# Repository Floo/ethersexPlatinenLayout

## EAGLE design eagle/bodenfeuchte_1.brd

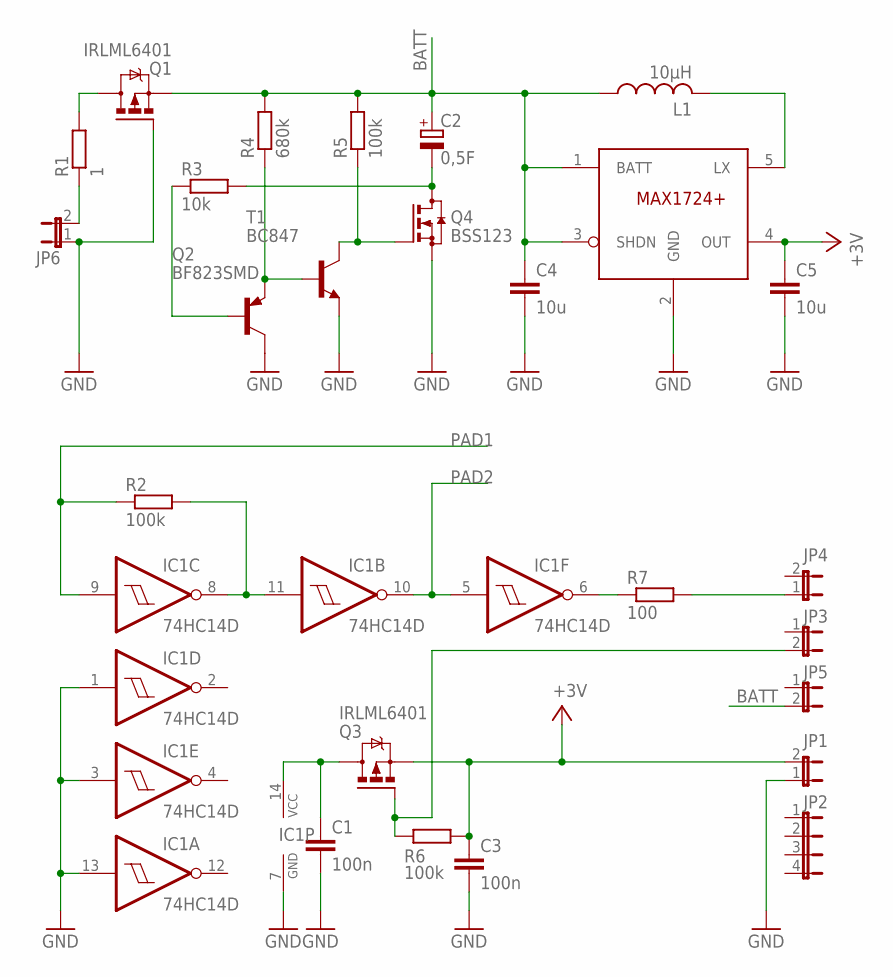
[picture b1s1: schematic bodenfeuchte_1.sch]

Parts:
C1, C3: 100n; C0805
C2: 0,5F; GOLDCAP5-21.5
C4, C5: 10u; C0805
IC1: 74HC14D; SO14
JP1, JP3, JP4, JP5, JP6: JP1E; JP1
JP2: JP4E; JP4
L1: 10µH; L1812
Q1, Q3: IRLML6401; MICRO3
Q2: BF823SMD; SOT23-BEC
Q4: BSS123; SOT23
R1: 1; R0805
R2, R5, R6: 100k; R0805
R3: 10k; R0805
R4: 680k; R0805
R7: 100; R0805
T1: BC847; SOT23
U$1: MAX1724; SOT23-5L

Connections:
BATT: C2.+, C4.1, JP5.2, L1.1, Q1.2 (S), R4.2, R5.2, U$1.1 (BATT), U$1.3 (SHDN)
GND: C1.2, C3.2, C4.2, C5.2, IC1.1 (I), IC1.3 (I), IC1.7 (GND), IC1.13 (I), JP1.1, JP6.1, Q1.1 (G), Q2.C, Q4.2 (S), T1.2 (E), U$1.2 (GND)
unnamed: IC1.8 (O), IC1.11 (I), R2.2
unnamed: IC1.6 (O), R7.1
unnamed: JP4.1, R7.2
unnamed: JP3.2, Q3.1 (G), R6.1
unnamed: C1.1, IC1.14 (VCC), Q3.3 (D)
unnamed: Q4.1 (G), R5.1, T1.3 (C)
unnamed: Q2.E, R4.1, T1.1 (B)
unnamed: C2.-, Q4.3 (D), R3.2
unnamed: Q2.B, R3.1
unnamed: JP6.2, R1.1
unnamed: Q1.3 (D), R1.2
unnamed: L1.2, U$1.5 (LX)
PAD1: IC1.9 (I), R2.1
PAD2: IC1.5 (I), IC1.10 (O)
V+: C3.1, C5.1, JP1.2, Q3.2 (S), R6.2, U$1.4 (OUT)

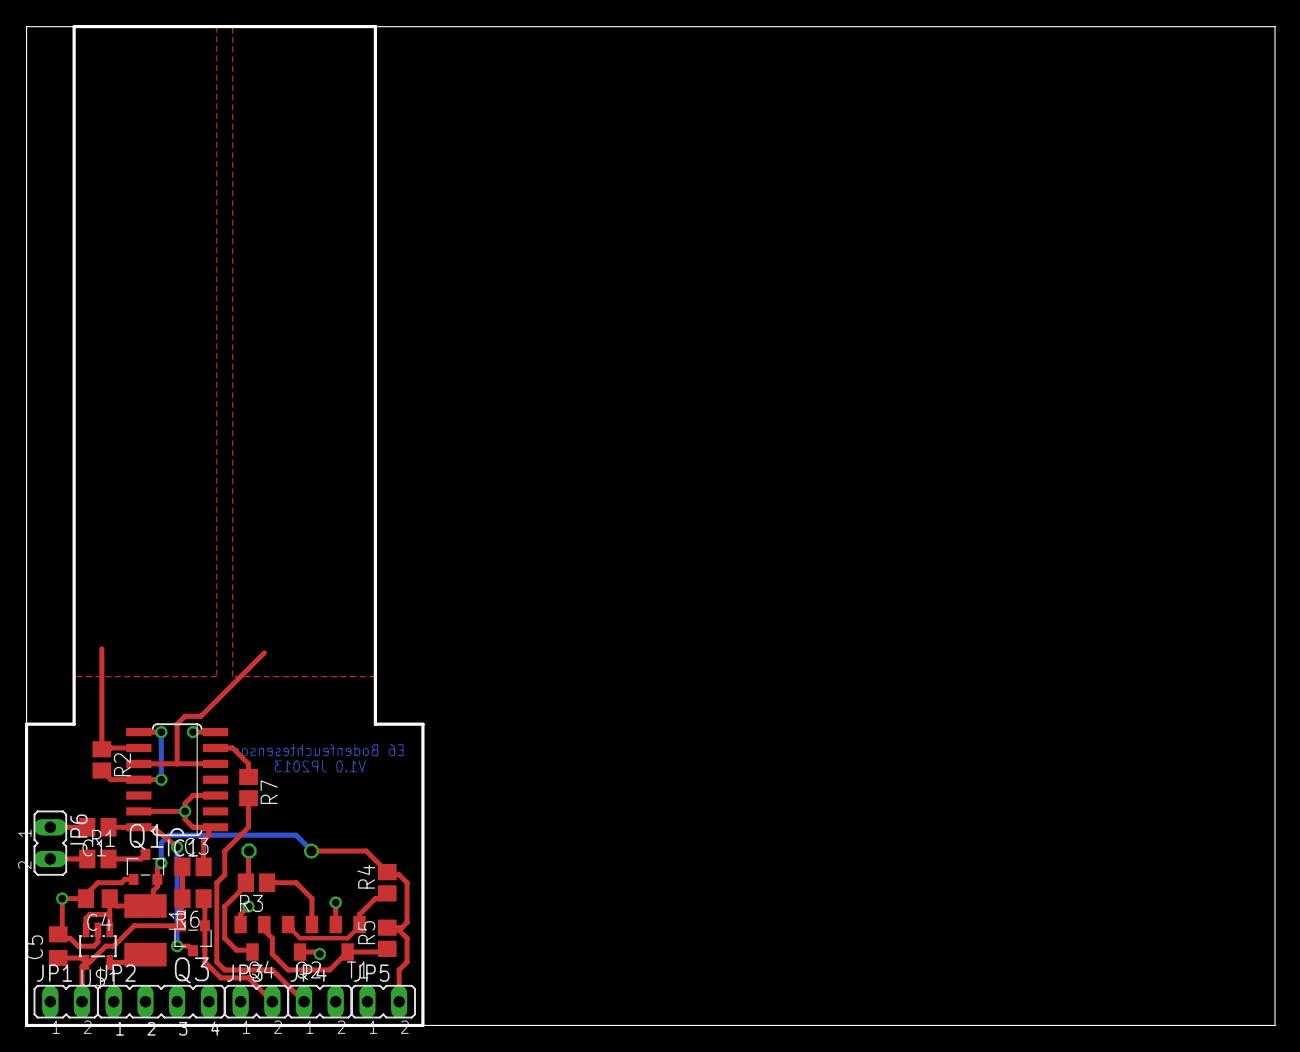
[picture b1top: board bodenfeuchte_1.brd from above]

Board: 2 copper layers, 99.9 x 80.0 mm, 26 parts (1 on the bottom side), 17 nets.

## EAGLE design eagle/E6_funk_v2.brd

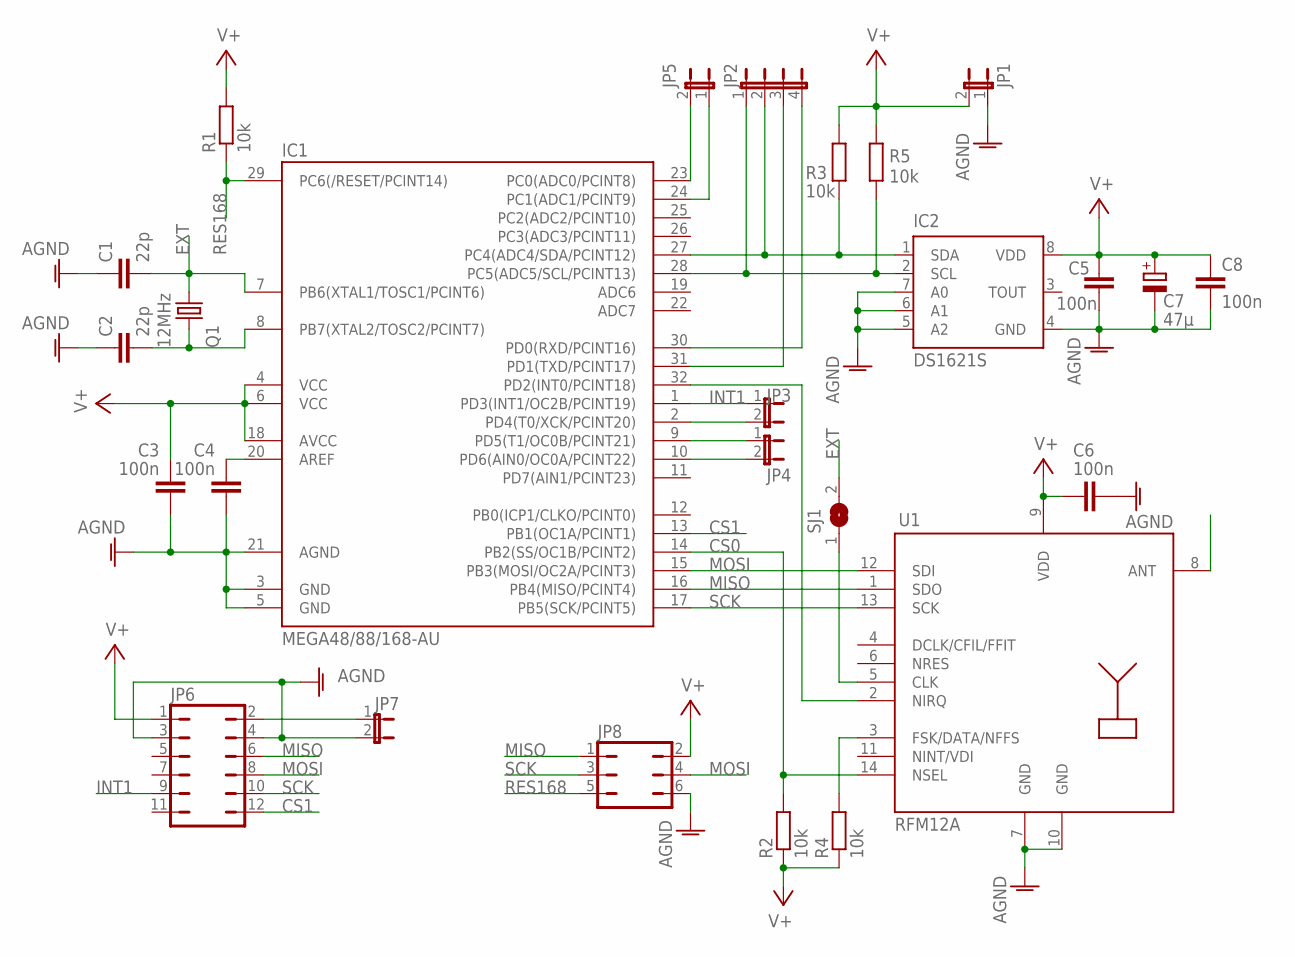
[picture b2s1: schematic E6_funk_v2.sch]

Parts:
C1, C2: 22p; C0805K
C3, C4, C5, C6, C8: 100n; C0805K
C7: 47µ; SMC_D
IC1: MEGA48/88/168-AU; TQFP32-08
IC2: DS1621S; SO08
JP1, JP3, JP4, JP5, JP7: JP1E; JP1
JP2: JP4E; JP4
JP6: JP6Q
JP8: JP3Q
Q1: 12MHz; CTS406
R1, R2, R3, R4, R5: 10k; R0805
SJ1: SJ
U1: RFM12A; RFM1

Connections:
ADC1: IC1.24 (PC1(ADC1/PCINT9)), JP5.1
AGND: C1.2, C2.2, C3.1, C4.1, C5.2, C6.1, C7.-, C8.2, IC1.3 (GND), IC1.5 (GND), IC1.21 (AGND), IC2.4 (GND), IC2.5 (A2), IC2.6 (A1), IC2.7 (A0), JP1.1, JP6.3, JP6.4, JP7.2, JP8.6, U1.7 (GND), U1.10 (GND)
CS0: IC1.14 (PB2(SS/OC1B/PCINT2)), R2.2, U1.14 (NSEL)
CS1: IC1.13 (PB1(OC1A/PCINT1)), JP6.12
EXT: C1.1, IC1.7 (PB6(XTAL1/TOSC1/PCINT6)), Q1.1, SJ1.2
INT1: IC1.1 (PD3(INT1/OC2B/PCINT19)), JP3.1, JP6.9
MISO: IC1.16 (PB4(MISO/PCINT4)), JP6.6, JP8.1, U1.1 (SDO)
MOSI: IC1.15 (PB3(MOSI/OC2A/PCINT3)), JP6.8, JP8.4, U1.12 (SDI)
unnamed: IC1.23 (PC0(ADC0/PCINT8)), JP5.2
unnamed: C2.1, IC1.8 (PB7(XTAL2/TOSC2/PCINT7)), Q1.3 (2)
unnamed: IC1.32 (PD2(INT0/PCINT18)), U1.2 (NIRQ)
unnamed: C4.2, IC1.20 (AREF)
unnamed: SJ1.1, U1.5 (CLK)
unnamed: R4.2, U1.3 (FSK/DATA/NFFS)
PD4: IC1.2 (PD4(T0/XCK/PCINT20)), JP3.2
PD5: IC1.9 (PD5(T1/OC0B/PCINT21)), JP4.1
PD6: IC1.10 (PD6(AIN0/OC0A/PCINT22)), JP4.2
RES168: IC1.29 (PC6(/RESET/PCINT14)), JP8.5, R1.1
RXD: IC1.30 (PD0(RXD/PCINT16)), JP2.4
SCK: IC1.17 (PB5(SCK/PCINT5)), JP6.10, JP8.3, U1.13 (SCK)
SCL: IC1.28 (PC5(ADC5/SCL/PCINT13)), IC2.2 (SCL), JP2.1, R5.1
SDA: IC1.27 (PC4(ADC4/SDA/PCINT12)), IC2.1 (SDA), JP2.2, R3.1
TXD: IC1.31 (PD1(TXD/PCINT17)), JP2.3
V+: C3.2, C5.1, C6.2, C7.+, C8.1, IC1.4 (VCC), IC1.6 (VCC), IC1.18 (AVCC), IC2.8 (VDD), JP1.2, JP6.1, JP8.2, R1.2, R2.1, R3.2, R4.1, R5.2, U1.9 (VDD)
VCC: JP6.2, JP7.1

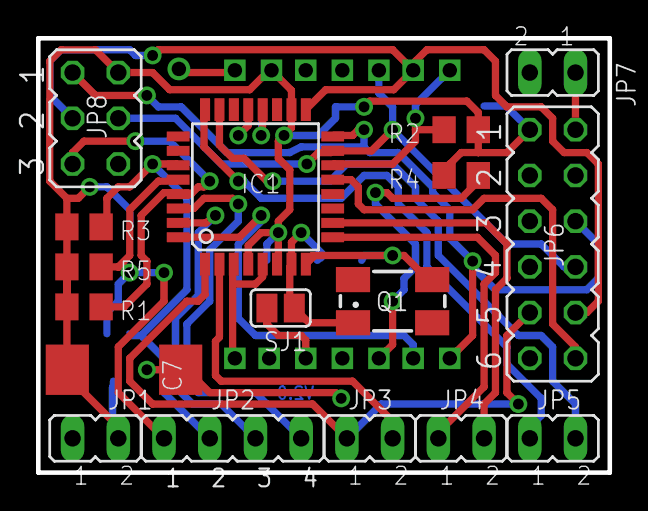
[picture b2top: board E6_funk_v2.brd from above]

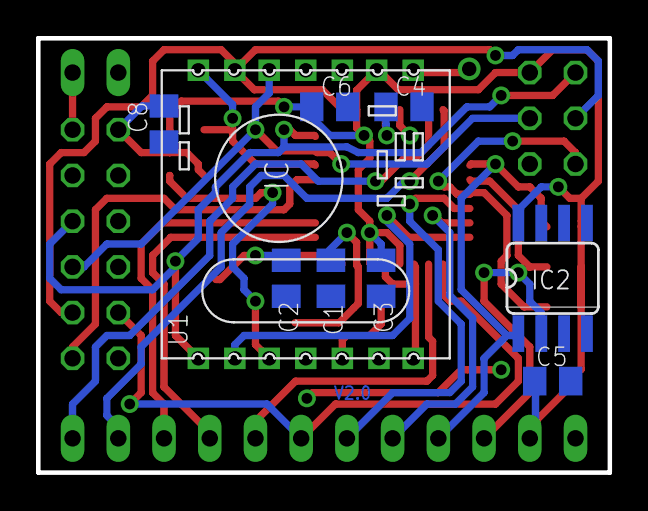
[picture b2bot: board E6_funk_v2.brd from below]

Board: 2 copper layers, 31.8 x 24.1 mm, 26 parts (9 on the bottom side), 25 nets.

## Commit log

2015-06-22 initial GIT commit
